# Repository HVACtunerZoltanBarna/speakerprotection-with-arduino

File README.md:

# speakerprotection-with-arduino
My Arduino based Speaker protection for 4 channels.
AVE !
I am happy to share my project with you. If you use or upgrade it I would be happy if you give some feeback to me just to see how it works around the world:).

So it is an arduino based speaker protection. I use it in my custom made amp, and works well from 2021. Simple and rigid...
You can find here kicad model as well.
What it does?
Protects the speaker from those current whose does not make movement. So protects it from burning.
Topology is:
Amplifier outputs max 4 channel. But can use for less. (An for more as well if you modify the code and use more analogInputs :) )
The voltage from amp output must go to a voltage divided RC filter.
If the AC contains too much DC (or the frequency is extremely low) that can be seen on the capacitor it opens a relay. Normally DC part of the current is 0 so the speakers can move and cool themself.
Just an advice. It is fine to calibrate the inputs with freq generator and power supply for example.
And dont forget about the input voltage of Arduino. The analogRead compares
voltage to Vref. If Supply is too low Vref will lower too.

Bye. Z. :)

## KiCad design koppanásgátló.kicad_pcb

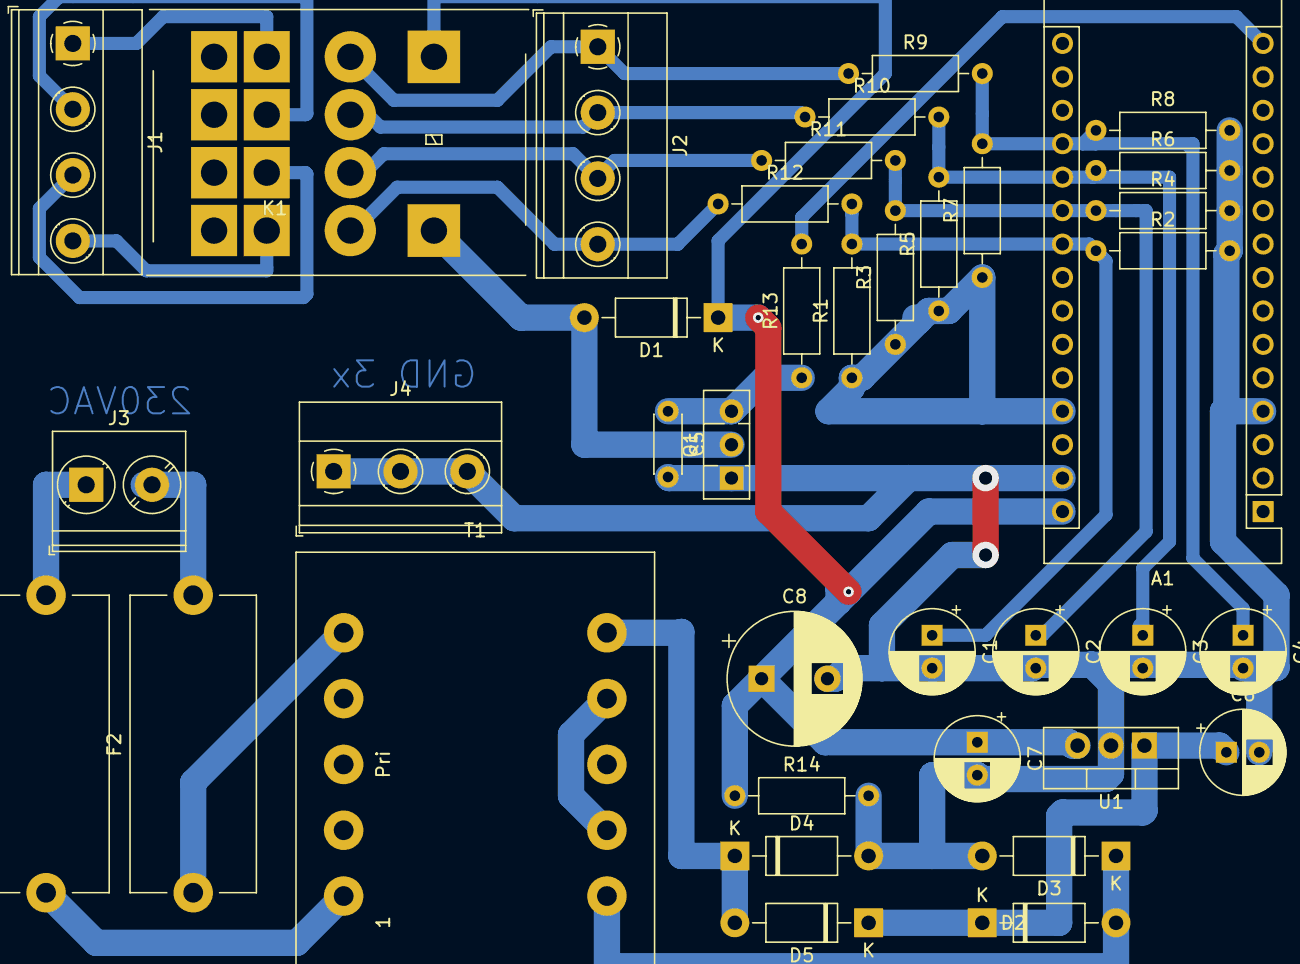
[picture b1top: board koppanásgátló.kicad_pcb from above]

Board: 2 copper layers, 38 parts (0 on the bottom side), 26 nets.

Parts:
A1: Arduino_Nano_v3.x; Arduino_Nano
C1, C2, C3, C4, C6, C7: 100uF; CP_Radial_D6.3mm_P2.50mm
C5: 1nF; C_Disc_D4.3mm_W1.9mm_P5.00mm
C8: 2200uF; CP_Radial_D10.0mm_P5.00mm
D1, D2, D3, D4, D5: 1N4001; D_DO-41_SOD81_P10.16mm_Horizontal
F1, F2: Fuse; Fuseholder_Cylinder-5x20mm_Stelvio-Kontek_PTF78_Horizontal_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
J1, J2: Conn_01x04_Female; TerminalBlock_Phoenix_MKDS-1,5-4_1x04_P5.00mm_Horizontal
J3: Conn_01x02_Female; TerminalBlock_Phoenix_PT-1,5-2-5.0-H_1x02_P5.00mm_Horizontal
J4: Conn_01x03_Female; TerminalBlock_Phoenix_MKDS-1,5-3-5.08_1x03_P5.08mm_Horizont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
K1: SCHRACK_PT570012; Relay_4PDT_SCHRACK_PT570012
Q1: BD135; TO-126-3_Vertical
R1, R2, R3, R4, R5, R6, R7, R8, R13: 10K; R_Axial_DIN0207_L6.3mm_D2.5mm_P10.16mm_Horizontal
R9, R10, R11, R12: 82K; R_Axial_DIN0207_L6.3mm_D2.5mm_P10.16mm_Horizontal
R14: 4K7; R_Axial_DIN0207_L6.3mm_D2.5mm_P10.16mm_Horizontal
T1: Transformer_1P_2S; Transformer_CHK_EI30-2VA_2xSec
U1: LM7812_TO220; TO-220-3_Vertical

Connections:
unnamed: A1.15, R13.2
unnamed: A1.19, C4.1, R7.2, R8.1, R9.2
unnamed: A1.20, C3.1, R5.2, R6.1, R10.2
unnamed: A1.21, C2.1, R3.2, R4.1, R11.2
unnamed: A1.22, C1.1, R1.2, R2.1, R12.2
unnamed: A1.27, R1.1, R3.1, R5.1, R7.1
unnamed: A1.4, A1.29, C1.2, C2.2, C3.2, C4.2, C5.2, C6.2, C7.2, C8.2, D3.2, D4.2, J4.1, J4.2, J4.3, Q1.1, R2.2, R4.2, R6.2, R8.2, R14.2, U1.2
unnamed: A1.30, C7.1, C8.1, D1.1, K1.A1, R14.1, U1.3
unnamed: C5.1, Q1.3, R13.1
unnamed: C6.1, D2.1, D5.1, U1.1
unnamed: D1.2, K1.A2, Q1.2
unnamed: D2.2, D3.1, T1.10
unnamed: D4.1, D5.2, T1.6
unnamed: F1.1, T1.1
unnamed: F1.2, J3.1
unnamed: F2.1, T1.5
unnamed: F2.2, J3.2
unnamed: J1.1, K1.14
unnamed: J1.2, K1.24
unnamed: J1.3, K1.34
unnamed: J1.4, K1.44
unnamed: J2.1, K1.11, R9.1
unnamed: J2.2, K1.21, R10.1
unnamed: J2.3, K1.31, R11.1
unnamed: J2.4, K1.41, R12.1
unnamed: T1.7, T1.9

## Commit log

2025-08-08 Add files via upload
    some words can be in Hungarian sorry...
